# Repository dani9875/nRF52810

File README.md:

# nRF52810
Basic HW and FW to setup nRF developer environment

# Instructions

1. Clone the repository:
```bash
git clone <repository-url>
```

2. Build the Docker image (requires sudo permissions):
```bash
sudo ./docker_build.sh
```
3. Start the Docker container:

```bash
./docker_start.sh
```

4. Enter the project root folder (you should already be in the correct directory).

5. Initialize the West workspace:
```bash
west init -l app
```

6. Update west modules (this step can take a few minutes)
```bash
west update
```

7. Export Zephyr environment:
```bash
west zephyr-export
```

8. Build the application for the nRF52840 DK:
```bash
west build -b nrf52840dk/nrf52840 app
```

## Release notes

### Version: v2.0-test phase
Changelog:
- 2.4 GHz antenna design
- LED for blinky funtionality
- Plug of nails changed to pluggable
- Optical sensor added
- 3V3 and 1V9 power rails
- KiCAD library commit: f8f82b3228b9b2e6a28c75499dfac7be01fe0e7f

### Version: v1.0
Changelog:
- Minimal env. for bringing an nRF52810 up
- LED for blinky functionality
- Tactile button for user input
- LDO power adjustment
- Plug of nails footprint faulty

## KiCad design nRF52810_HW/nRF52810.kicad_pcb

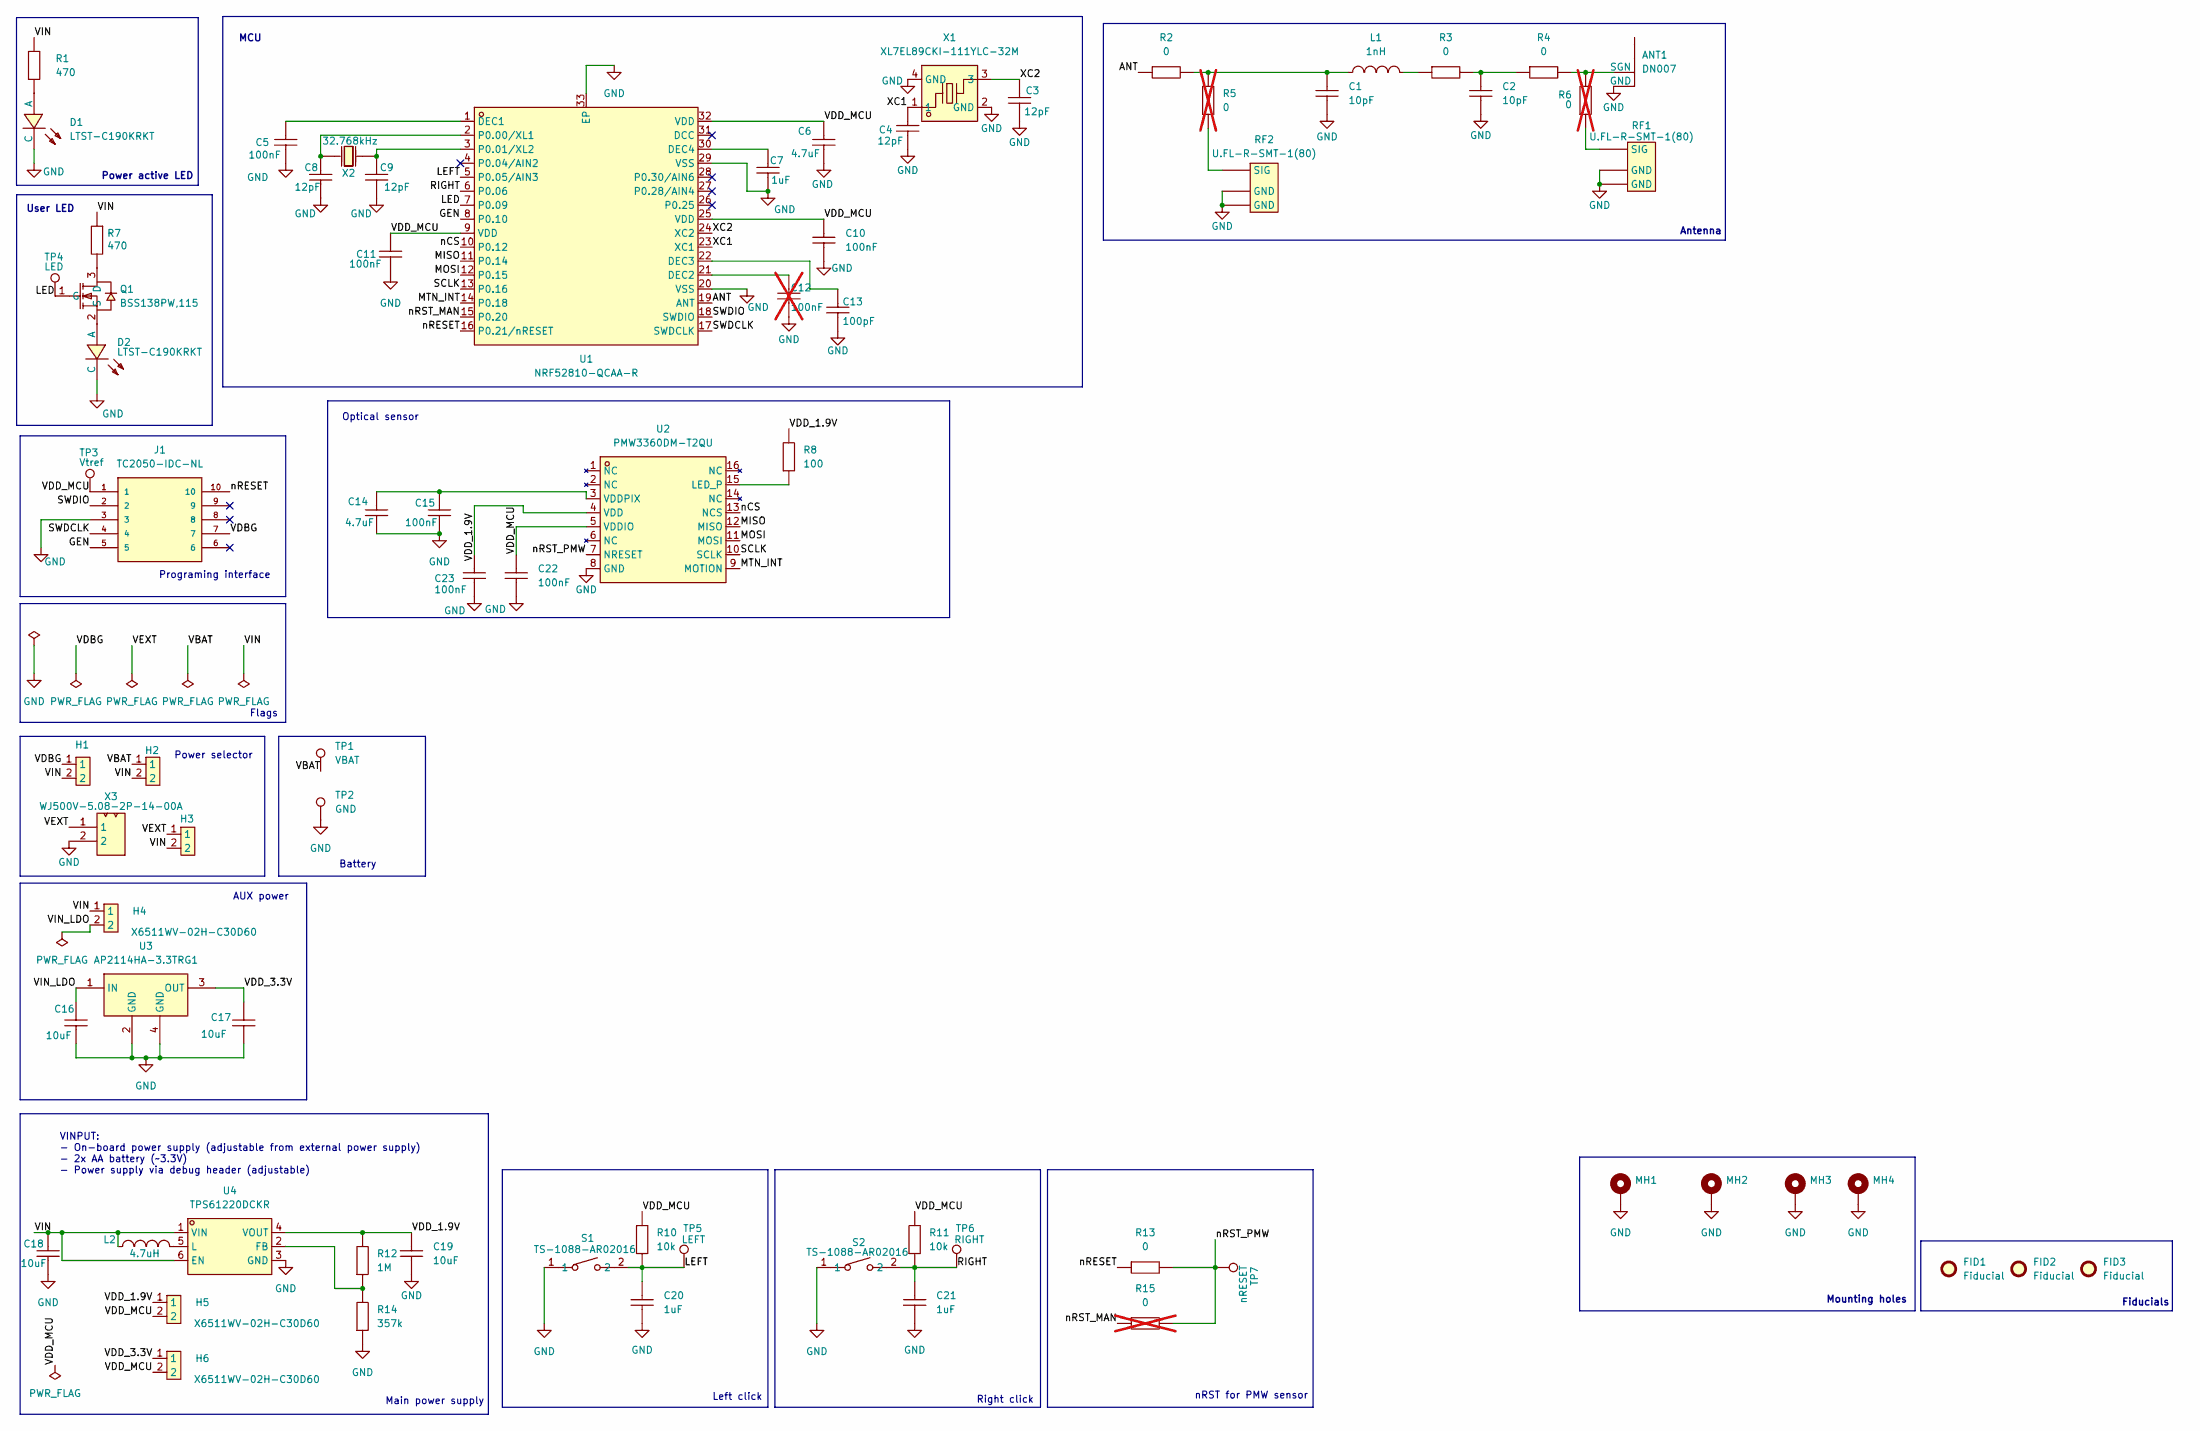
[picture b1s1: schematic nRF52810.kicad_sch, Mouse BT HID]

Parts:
ANT1: DN007; [ANTENNA]DN007_1,2.4GHz
C1, C2: C0805C100K5GACTU; [CAP_SMD_0805_2012Metric]; LCSC Part C2181972
C3, C4, C8, C9: C0805C120J5GACAUTO; [CAP_SMD_0805_2012Metric]; LCSC Part C3844403
C5, C10, C11, C15, C22, C23: CC0805KRX7R9BB104; [CAP_SMD_0805_2012Metric]; LCSC Part C49678
C6, C14: CL21A475KAQNNNE; [CAP_SMD_0805_2012Metric]; LCSC Part C1779
C7, C20, C21: C0805C105M4VACTU; [CAP_SMD_0805_2012Metric]; LCSC Part C2171722
C12: CC0805KRX7R9BB104; [CAP_SMD_0805_2012Metric]; LCSC Part C49678; not fitted
C13: C0805C101K5GACTU; [CAP_SMD_0805_2012Metric]; LCSC Part C452752
C16, C17, C18, C19: CL21A106KOQNNNE; [CAP_SMD_0805_2012Metric]; LCSC Part C1713
D1, D2: LTST-C190KRKT; [LED]Lite-On LTST-C190KRKT; LCSC Part C94869
FID1, FID2, FID3: Fiducial; Fiducial_0.5mm_Mask1mm
H1, H2, H3, H4, H5, H6: X6511WV-02H-C30D60; [2x1_PIN_HEADER_STR]XKB Connection X6511WV-02H-C60D30; LCSC Part C706874
J1: TC2050-IDC-NL; [PLUG_OF_NAILS_10P]TC2050_IDC_NL; PARTREV A
L1: LQG15HS1N0S02D; [IND_SMD_0402_1005Metric]; LCSC Part C18222
L2: FNR3015S4R7MT; [POWER_IND]cjiang (Changjiang Microelectronics Tech) FNR301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; LCSC Part C167753
MH1, MH2, MH3, MH4: [MOUNTING_HOLE]MountingHole_2.2mm_M2_DIN965_Pad
Q1: BSS138PW,115; [NMOS]Nexperia BSS138PW,115; LCSC Part C193366
R1, R7: 0805W8F4700T5E; [RES_SMD_0805_2012Metric]; LCSC Part C17710
R2, R3, R4: 0402WGF0000TCE; [RES_SMD_0402_1005Metric]; LCSC Part C17168
R5, R6: 0402WGF0000TCE; [RES_SMD_0402_1005Metric]; LCSC Part C17168; not fitted
R8: 0805W8F1000T5E; [RES_SMD_0805_2012Metric]; LCSC Part C17408
R10, R11: 0805W8F1002T5E; [RES_SMD_0805_2012Metric]; LCSC Part C17414
R12: 0805W8F1004T5E; [RES_SMD_0805_2012Metric]; LCSC Part C17514
R13: 0805W8F0000T5E; [RES_SMD_0805_2012Metric]; LCSC Part C17673
R14: RK73H2ATTD3573F; [RES_SMD_0805_2012Metric]; LCSC Part C317468
R15: 0805W8F0000T5E; [RES_SMD_0805_2012Metric]; LCSC Part C17673; not fitted
RF1, RF2: U.FL-R-SMT-1(80); [SMD_COAXIAL_CONNECTOR]HRS(Hirose) U.FL-R-SMT-1(80); LCSC Part C88374
S1, S2: TS-1088-AR02016; [TACTILE_SWITCH]XUNPU TS-1088-AR02016; LCSC Part C720477
TP1: VBAT; [TEST_POINT]TestPoint_Pad_2.0x2.0mm
TP2: GND; [TEST_POINT]TestPoint_Pad_2.0x2.0mm
TP3: Vtref; [TEST_POINT]TestPoint_Pad_D1.0mm
TP4: LED; [TEST_POINT]TestPoint_Pad_D1.0mm
TP5: LEFT; [TEST_POINT]TestPoint_Pad_D1.0mm
TP6: RIGHT; [TEST_POINT]TestPoint_Pad_D1.0mm
TP7: nRESET; [TEST_POINT]TestPoint_Pad_D1.0mm
U1: NRF52810-QCAA-R; [MCU]Nordic Semicon nRF52810-QCAA-R; LCSC Part C519278
U2: PMW3360DM-T2QU; [OPTICAL_NAVIGATION_CHIP]PixArt PMW3360DM-T2QU; LCSC Part C20612443
U3: AP2114HA-3.3TRG1; [LDO]Diodes Incorporated AP2114HA-3.3TRG1; LCSC Part C460314
U4: TPS61220DCKR; [BOOST_CONV]Texas Instruments TPS61220DCKR; LCSC Part C15421
X1: XL7EL89CKI-111YLC-32M; [Crystal_32_MHz]YXC XL7EL89CKI-111YLC-32M; LCSC Part C2965582
X2: SC-20S32.768kHz20PPM9pF; [Crystal_32_768_kHZ]Seiko SC-20S,32.768kHz,20PPM,9pF; LCSC Part C97603
X3: WJ500V-5.08-2P-14-00A; [1x2_SCREW_TERMINAL_BLOCK]Ningbo Kangnex Elec WJ500V-5.08-2P; LCSC Part C8465

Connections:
/ANT: R2.1, U1.19 (ANT)
/GEN: J1.5, U1.8 (P0.10)
/LED: Q1.1 (G), TP4.1, U1.7 (P0.09)
/LEFT: C20.2, R10.1, S1.2, TP5.1, U1.5 (P0.05/AIN3)
/MISO: U1.11 (P0.14), U2.12 (MISO)
/MOSI: U1.12 (P0.15), U2.11 (MOSI)
/MTN_INT: U1.14 (P0.18), U2.9 (MOTION)
/RIGHT: C21.2, R11.1, S2.2, TP6.1, U1.6 (P0.06)
/SCLK: U1.13 (P0.16), U2.10 (SCLK)
/SWDCLK: J1.4, U1.17 (SWDCLK)
/SWDIO: J1.2, U1.18 (SWDIO)
/VBAT: H2.1, TP1.1
/VDBG: H1.1, J1.7
/VDD_1.9V: C19.2, C23.2, H5.1, R8.2, R12.2, U2.4 (VDD), U4.4 (VOUT)
/VDD_3.3V: C17.2, H6.1, U3.3 (OUT)
/VDD_MCU: C6.2, C10.2, C11.2, C22.2, H5.2, H6.2, J1.1, R10.2, R11.2, TP3.1, U1.9 (VDD), U1.25 (VDD), U1.32 (VDD), U2.5 (VDDIO)
/VEXT: H3.1, X3.1
/VIN: C18.2, H1.2, H2.2, H3.2, H4.1, L2.2, R1.1, R7.1, U4.1 (VIN), U4.6 (EN)
/VIN_LDO: C16.2, H4.2, U3.1 (IN)
/XC1: C4.2, U1.23 (XC1), X1.1
/XC2: C3.2, U1.24 (XC2), X1.3
/nCS: U1.10 (P0.12), U2.13 (NCS)
/nRESET: J1.10, R13.1, U1.16 (P0.21/nRESET)
/nRST_MAN: R15.1, U1.15 (P0.20)
/nRST_PMW: R13.2, R15.2, TP7.1, U2.7 (NRESET)
GND: ANT1.1 (GND), C1.1, C2.1, C3.1, C4.1, C5.1, C6.1, C7.1, C8.1, C9.1, C10.1, C11.1, C12.1, C13.1, C14.2, C15.1, C16.1, C17.1, C18.1, C19.1, C20.1, C21.1, C22.1, C23.1, D1.2 (C), D2.2 (C), J1.3, MH1.1, MH2.1, MH3.1, MH4.1, R14.1, RF1.2 (GND), RF1.3 (GND), RF2.2 (GND), RF2.3 (GND), S1.1, S2.1, TP2.1, U1.20 (VSS), U1.29 (VSS), U1.33 (EP), U2.8 (GND), U3.2 (GND), U3.4 (GND), U4.3 (GND), X1.2 (GND), X1.4 (GND), X3.2
unnamed: ANT1.2 (SGN), R4.2, R6.2
unnamed: C1.2, L1.2, R2.2, R5.2
unnamed: C2.2, R3.2, R4.1
unnamed: D1.1 (A), R1.2
unnamed: D2.1 (A), Q1.2 (S)
unnamed: L1.1, R3.1
unnamed: Q1.3 (D), R7.2
unnamed: R6.1, RF1.1 (SIG)
unnamed: R5.1, RF2.1 (SIG)
unnamed: C5.2, U1.1 (DEC1)
unnamed: C12.2, U1.21 (DEC2)
unnamed: C13.2, U1.22 (DEC3)
unnamed: C7.2, U1.30 (DEC4)
unnamed: C8.2, U1.2 (P0.00/XL1), X2.1
unnamed: C9.2, U1.3 (P0.01/XL2), X2.2
unnamed: R8.1, U2.15 (LED_P)
unnamed: C14.1, C15.2, U2.3 (VDDPIX)
unnamed: R12.1, R14.2, U4.2 (FB)
unnamed: L2.1, U4.5 (L)

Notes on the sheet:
Right click
User LED
Power active LED
nRST for PMW sensor
Programing interface
Left click
Flags
Mounting holes
Fiducials
Antenna
Optical sensor
AUX power
MCU
VINPUT: - On-board power supply (adjustable from external power supply) - 2x AA battery (~3.3V) - Power supply via debug header (adjustable)
Main power supply
Power selector
Battery

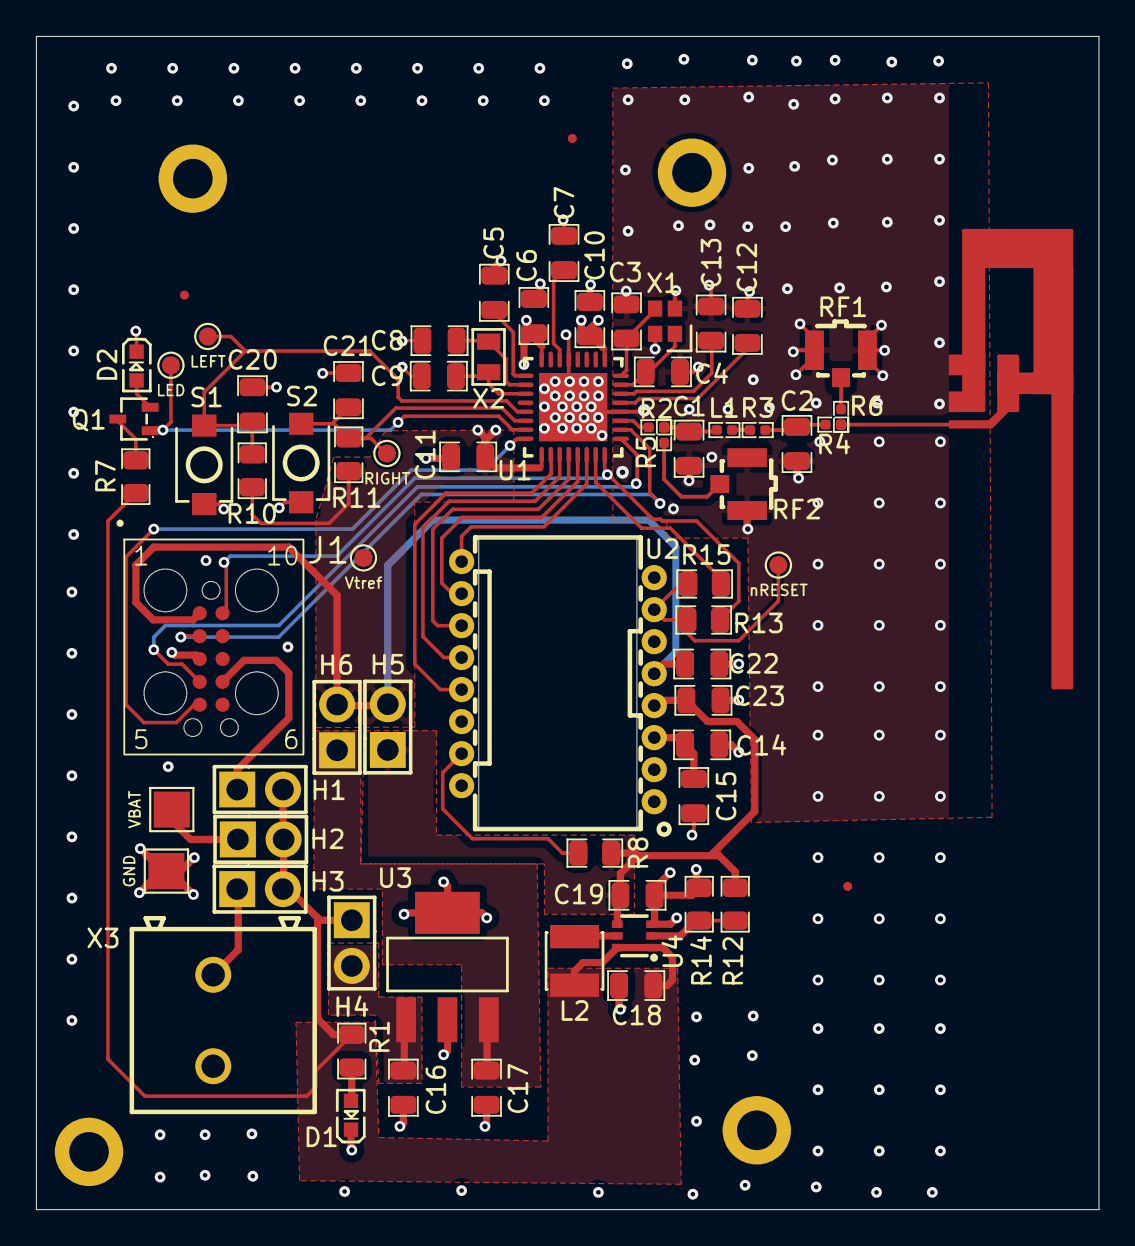
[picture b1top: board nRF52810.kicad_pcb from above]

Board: 4 copper layers, 59.0 x 65.2 mm, 75 parts (0 on the bottom side), 45 nets.

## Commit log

2024-07-01 Kibot config added
2024-07-24 testing
2024-07-24 First usable build with a custom board from sample example project
2024-07-27 Custom plank board renamed
2024-07-27 Working blinking example
2024-07-28 Workflow and gitignore expand
2024-07-30 commit++
2024-10-09 Latest
2025-01-03 Considerate changes
2025-01-03 First draft design
2025-01-12 Refactoring build envrionment
2025-01-12 HID migration
2025-01-12 .gitignore expanded
2025-01-13 Full project build
2025-02-10 bump large
2025-02-11 Bulk change
2025-02-12 test_phase
2025-02-12 Release notes to test phase
2025-02-13 Custom board run from zephyr directory
2025-02-13 chkpt
2025-02-15 Custom buildable board with BT
2025-02-15 DTSI changes
2025-02-28 LED blinking verified
2025-02-28 working bt example with nrfConnect
2025-03-31 SPI comm on, but PMW does not react
